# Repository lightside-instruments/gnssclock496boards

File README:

The gnssclock496boards is an open hardware extension module for Ultra96
or other 96boards CE compatible devices. It uses the u-blox LEA-M8T
module or other LEA-* compatible modules.

In addition to a 1 sec PPS signal which is available on almost all
GNSS boards it has high frequency (e.g. 10 MHz clock signal) that
can be used for better precision timestamp or frequency synchronization.

Published by Lightside Instruments AS.

The initial release gnssclock496boards-1.0 includes schematic and PCB
design files for KiCAD.

The project is published by Lightside Instruments AS
under TAPR Open Hardware License. Read the LICENSE file
for details.

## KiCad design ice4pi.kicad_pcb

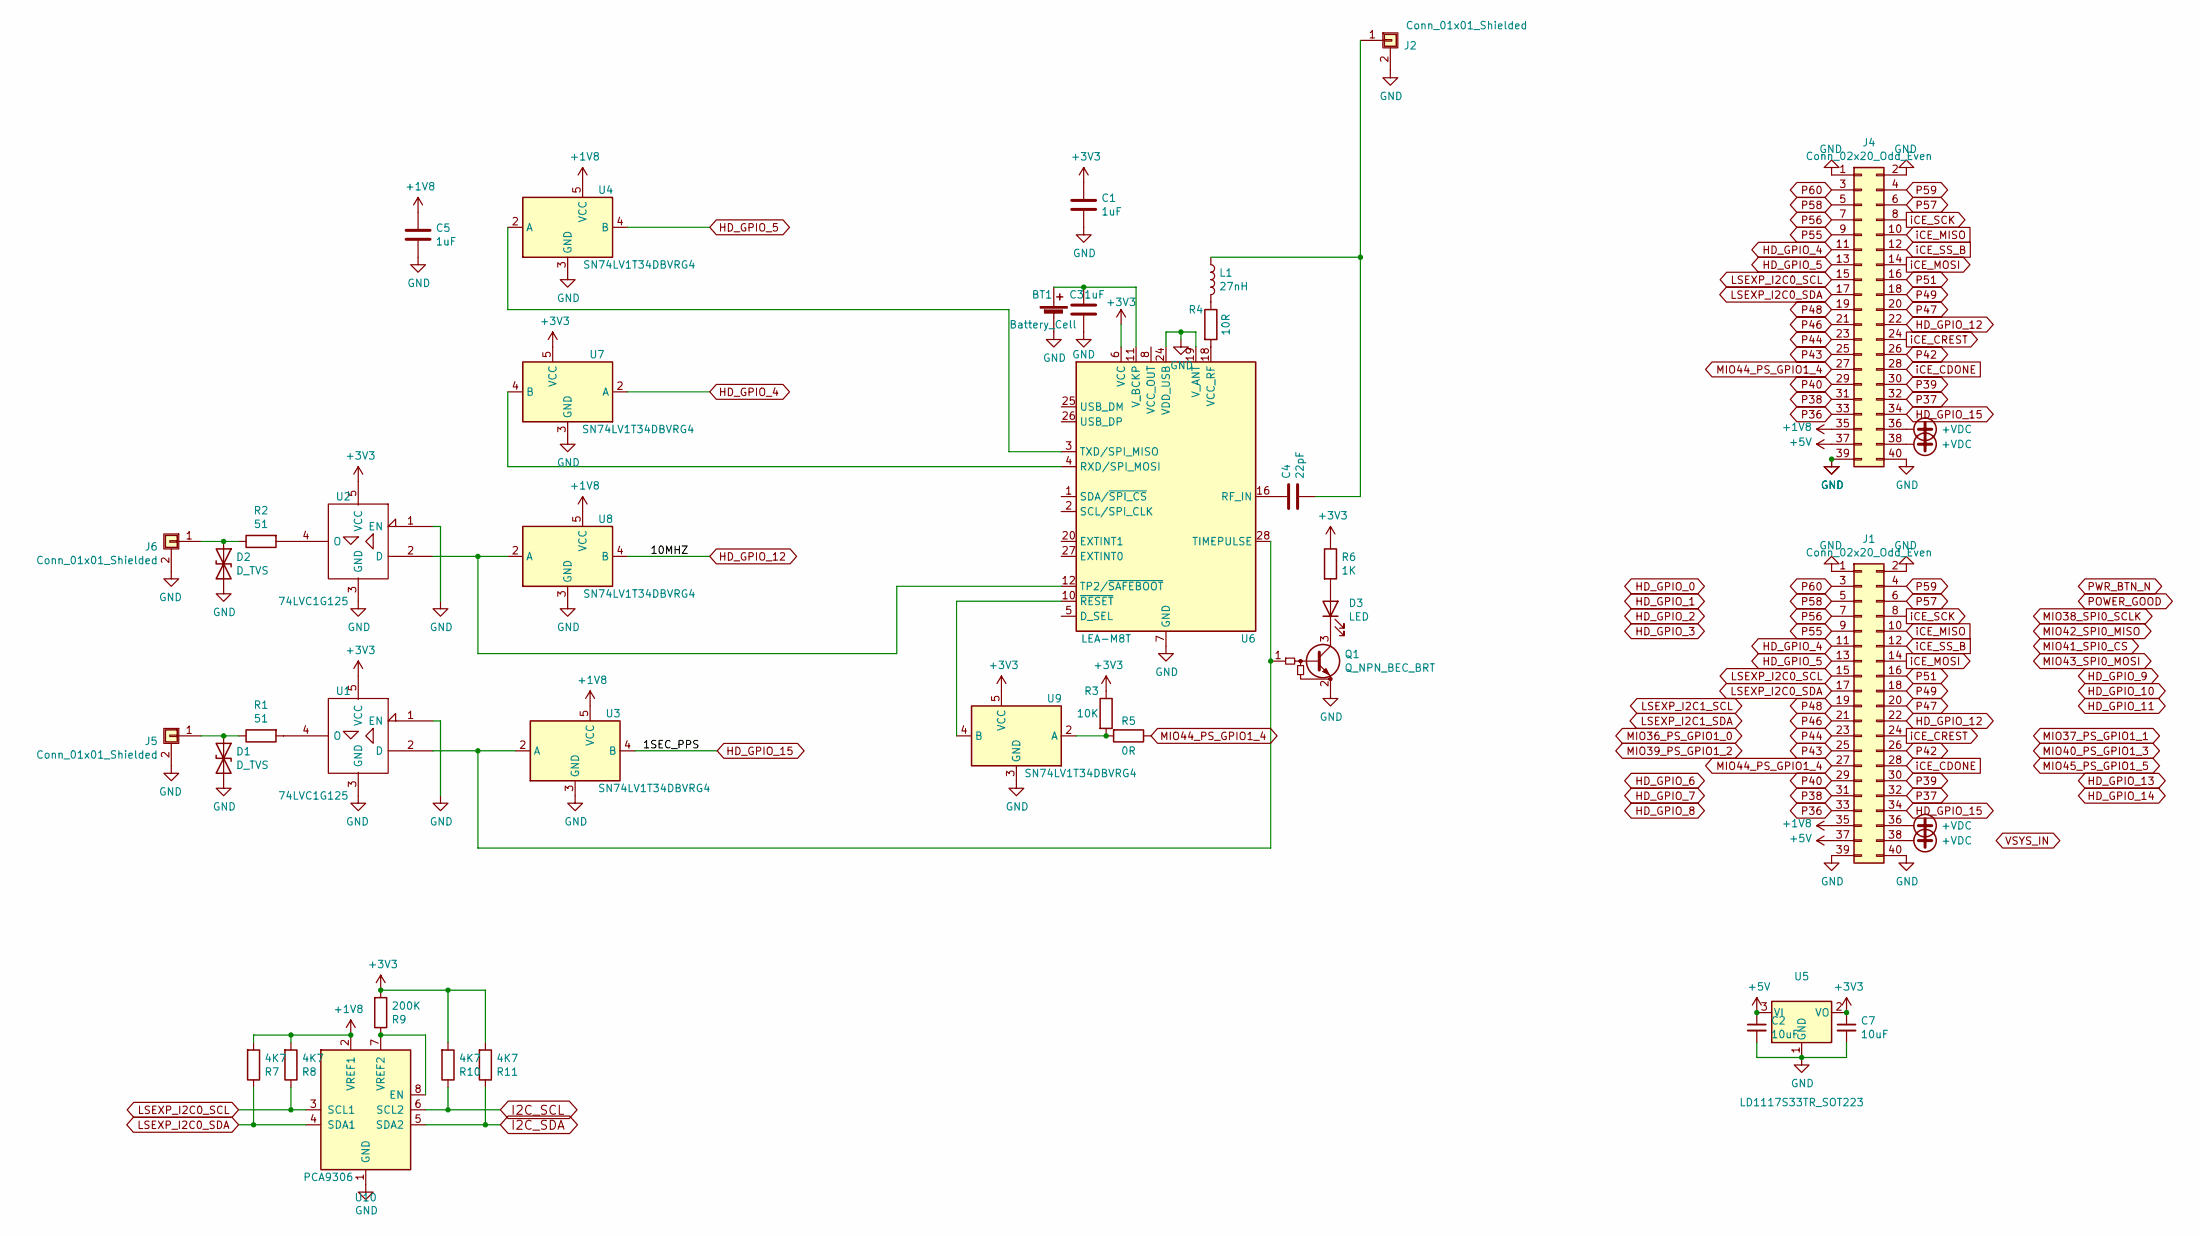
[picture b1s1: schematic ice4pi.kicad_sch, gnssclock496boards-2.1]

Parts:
BT1: Battery_Cell; BatteryHolder_Keystone_2450
C1, C5: 1uF; R_0402_1005Metric
C2, C7: 10uF; C_0402_1005Metric
C3: 1uF; C_0402_1005Metric
C4: 22pF; L_0402_1005Metric
D1, D2: D_TVS; R_0402_1005Metric
D3: LED; D_0603_1608Metric
J1: Conn_02x20_Odd_Even; Socket_Strip_SMD_2x20_Pitch2mm
J2, J5, J6: Conn_01x01_Shielded; SMA_LINX_CONSMA002_Horizontal
J4: Conn_02x20_Odd_Even; Pin_Header_SMD_2x20_Pitch2mm
L1: 27nH; L_0402_1005Metric
Q1: Q_NPN_BEC_BRT; SOT-323_SC-70
R1, R2: 51; R_0805_2012Metric
R3: 10K; R_0402_1005Metric
R4: 10R; R_1206_3216Metric
R5: 0R; R_0402_1005Metric
R6: 1K; R_0402_1005Metric
R7, R8, R10, R11: 4K7; R_0402_1005Metric
R9: 200K; R_0402_1005Metric
U1, U2: 74LVC1G125; TSOP-5_1.65x3.05mm_P0.95mm
U3, U4, U7, U8, U9: SN74LV1T34DBVRG4; SOT-23-5
U5: LD1117S33TR_SOT223; SOT-223-3_TabPin2
U6: LEA-M8T; ublox_LEA
U10: PCA9306; SO-8_3.9x4.9mm_P1.27mm

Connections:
+1V8: C5.1, J1.35, J4.35, R7.2, R8.2, U3.5 (VCC), U4.5 (VCC), U8.5 (VCC), U10.2 (VREF1)
+3V3: C1.1, C7.1, R3.1, R6.1, R9.2, R10.2, R11.2, U1.5 (VCC), U2.5 (VCC), U5.2 (VO), U6.6 (VCC), U7.5 (VCC), U9.5 (VCC)
+5V: C2.1, J1.37, J4.37, U5.3 (VI)
+VDC: J1.36, J1.38, J4.36, J4.38
GND: BT1.2 (-), C1.2, C2.2, C3.2, C5.2, C7.2, D1.2 (A2), D2.2 (A2), J1.1, J1.2, J1.39, J1.40, J2.2 (Shield), J4.1, J4.2, J4.39, J4.40, J5.2 (Shield), J6.2 (Shield), Q1.2 (E), U1.1 (EN), U1.3 (GND), U2.1 (EN), U2.3 (GND), U3.3 (GND), U4.3 (GND), U5.1 (GND), U6.7 (GND), U6.13 (GND), U6.14 (GND), U6.15 (GND), U6.17 (GND), U6.19 (V_ANT), U6.24 (VDD_USB), U7.3 (GND), U8.3 (GND), U9.3 (GND), U10.1 (GND)
HD_GPIO_4: J1.11, J4.11, U7.2 (A)
HD_GPIO_5: J1.13, J4.13, U4.4 (B)
HD_GPIO_12: J1.22, J4.22, U8.4 (B)
HD_GPIO_15: J1.34, J4.34, U3.4 (B)
I2C_SCL: R10.1, U10.6 (SCL2)
I2C_SDA: R11.1, U10.5 (SDA2)
LSEXP_I2C0_SCL: J1.15, J4.15, R8.1, U10.3 (SCL1)
LSEXP_I2C0_SDA: J1.17, J4.17, R7.1, U10.4 (SDA1)
MIO44_PS_GPIO1_4: J1.27, J4.27, R5.1
unnamed: BT1.1 (+), C3.1, U6.11 (V_BCKP)
unnamed: C4.1, U6.16 (RF_IN)
unnamed: C4.2, J2.1, L1.1
unnamed: D1.1 (A1), J5.1, R1.1
unnamed: D2.1 (A1), J6.1, R2.1
unnamed: D3.1 (K), Q1.3 (C)
unnamed: D3.2 (A), R6.2
unnamed: L1.2, R4.1
unnamed: Q1.1 (B), U1.2 (D), U3.2 (A), U6.28 (TIMEPULSE)
unnamed: R1.2, U1.4 (O)
unnamed: R2.2, U2.4 (O)
unnamed: R3.2, R5.2, U9.2 (A)
unnamed: R4.2, U6.18 (VCC_RF)
unnamed: R9.1, U10.7 (VREF2), U10.8 (EN)
unnamed: U2.2 (D), U6.12 (TP2/~SAFEBOOT), U8.2 (A)
unnamed: U4.2 (A), U6.3 (TXD/SPI_MISO)
unnamed: U6.4 (RXD/SPI_MOSI), U7.4 (B)
unnamed: U6.10 (~RESET), U9.4 (B)
P36: J1.33, J4.33
P37: J1.32, J4.32
P38: J1.31, J4.31
P39: J1.30, J4.30
P40: J1.29, J4.29
P42: J1.26, J4.26
P43: J1.25, J4.25
P44: J1.23, J4.23
P46: J1.21, J4.21
P47: J1.20, J4.20
P48: J1.19, J4.19
P49: J1.18, J4.18
P51: J1.16, J4.16
P55: J1.9, J4.9
P56: J1.7, J4.7
P57: J1.6, J4.6
P58: J1.5, J4.5
P59: J1.4, J4.4
P60: J1.3, J4.3
iCE_CDONE: J1.28, J4.28
iCE_CREST: J1.24, J4.24
iCE_MISO: J1.10, J4.10
iCE_MOSI: J1.14, J4.14
iCE_SCK: J1.8, J4.8
iCE_SS_B: J1.12, J4.12

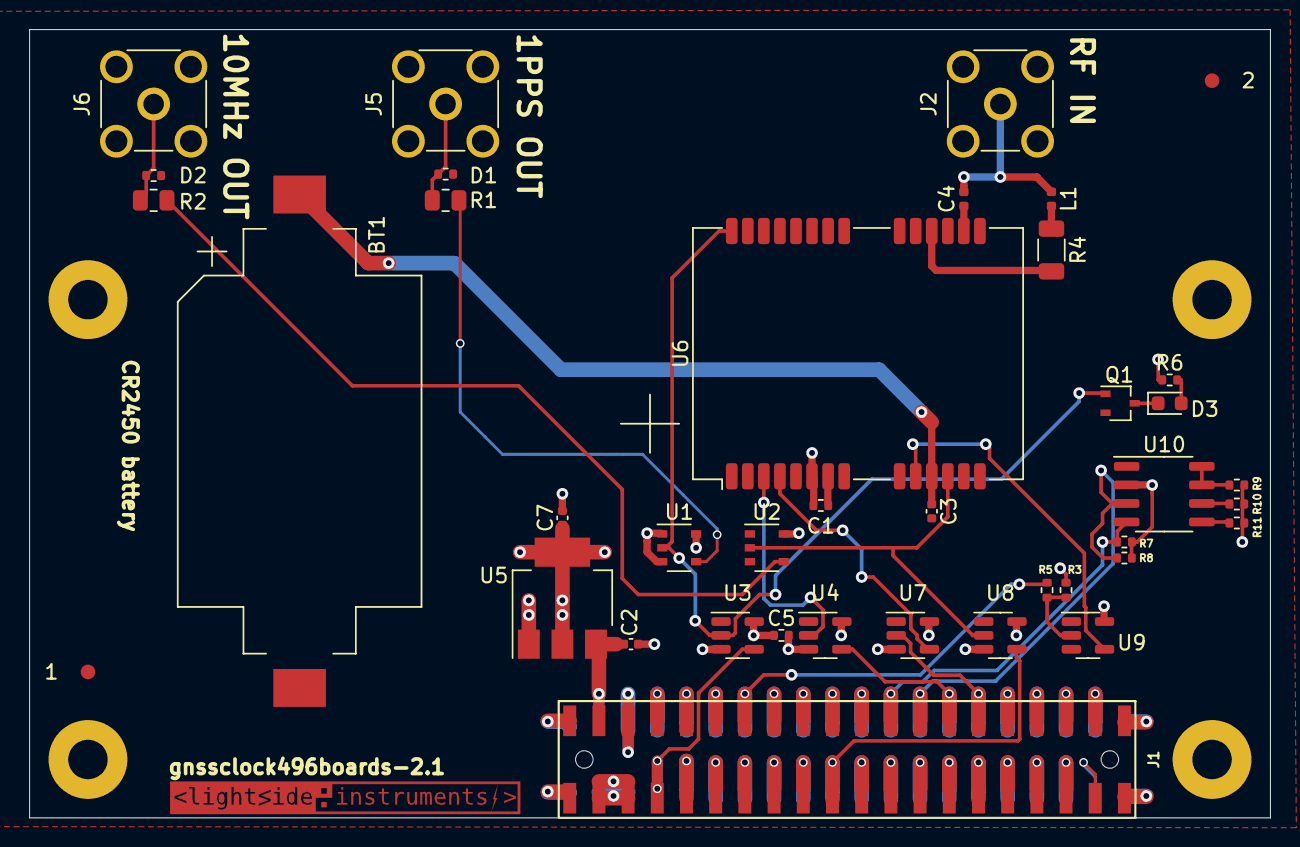
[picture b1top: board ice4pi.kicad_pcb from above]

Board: 4 copper layers, 85.0 x 54.0 mm, 45 parts (1 on the bottom side), 57 nets.

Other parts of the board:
1, 2: Fiducial_1mm_Mask3mm
M0, M1, M2, M2#2: MountingHole_2.7mm_Pad
svg2mod: G***; lsi-logo-24mm

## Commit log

2023-10-07 Release gnssclock496boards-1.0
2023-10-07 Release gnssclock496boards-2.0
2023-10-07 Release gnssclock496boards-2.1
